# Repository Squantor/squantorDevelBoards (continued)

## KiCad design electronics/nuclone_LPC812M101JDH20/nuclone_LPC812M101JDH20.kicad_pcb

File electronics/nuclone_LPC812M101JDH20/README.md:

# Nuclone development board for LPC812M101JD20
LPC812 development board inspired by the nucleo series from STM32.
## TODO's
Still some things need to be done:
* update Readme.md with pictures and BOM (WIP)

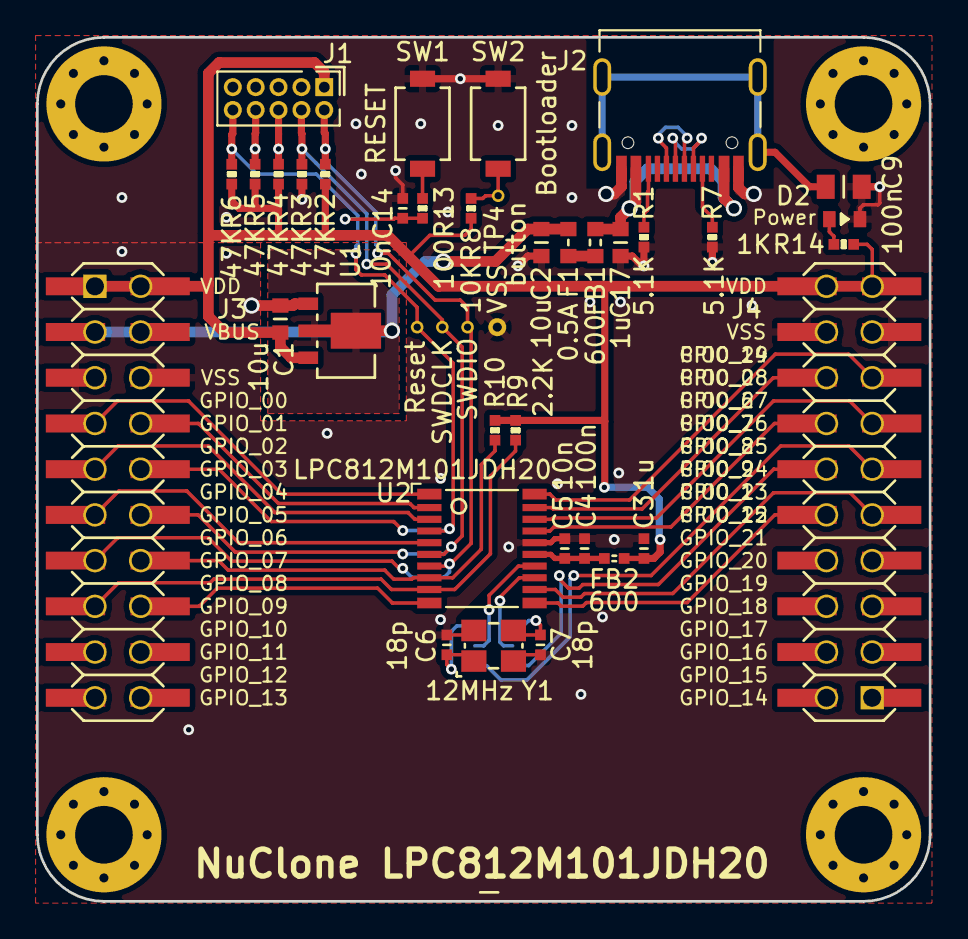
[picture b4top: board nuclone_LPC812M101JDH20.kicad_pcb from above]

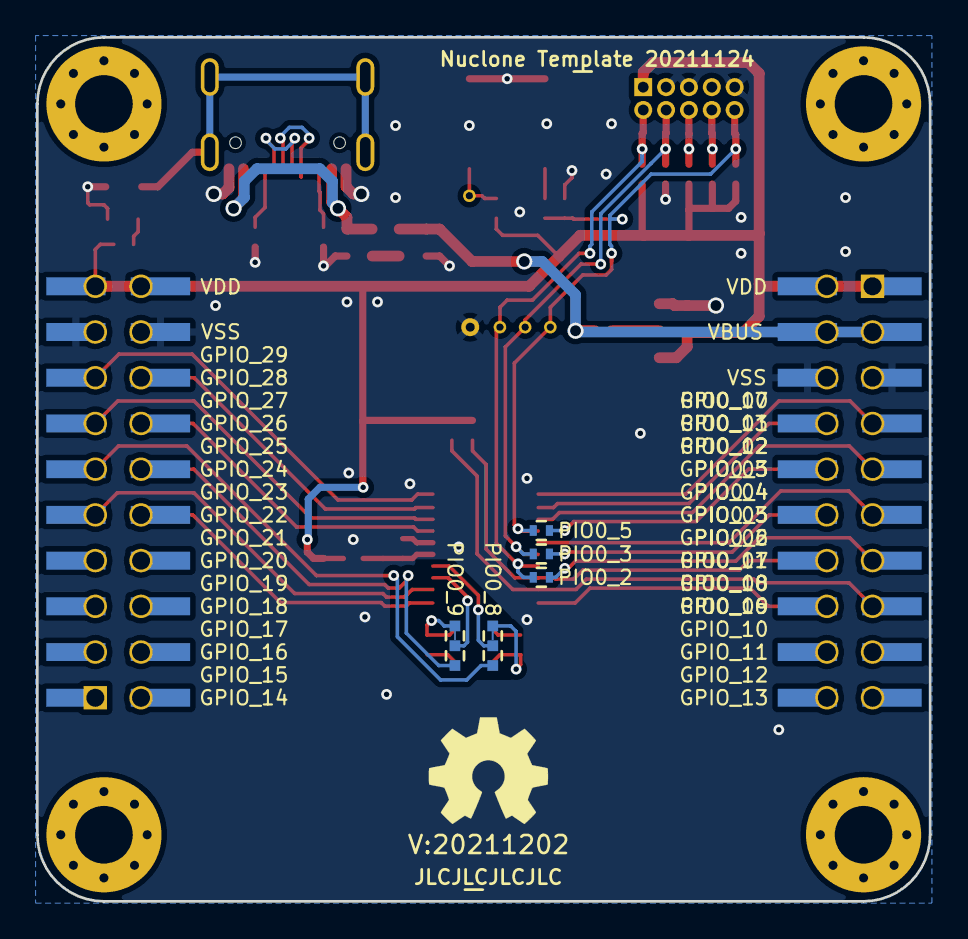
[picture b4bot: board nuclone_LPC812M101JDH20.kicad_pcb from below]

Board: 2 copper layers, 49.6 x 48.0 mm, 54 parts (9 on the bottom side), 41 nets.

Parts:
C1, C2: 10u; C_0603
C3: 1u; C_0402
C4: 100n; C_0402
C5, C14: 10n; C_0402
C6, C7: 18p; C_0402
C9: 100n; C_0805
C17: 1u; C_0603
D2: GREEN; LED_0603_hand
F1: 0.5A; F_0603_hand
FB1: 600; L_0603
FB2: 600; L_0402
H1, H2, H3, H4: MountingHole; MountingHole_3.2mm_M3_Pad_Via
J1: JTAG_2X05; Header-0127-2X05-H006
J2: TYPE-C-31-M-12; USB-C-HRO-31-M-12
J3: nuclone_small_left; nuclone_small_left_stacked
J4: nuclone_small_right; nuclone_small_right_stacked
JP1: PIO0_5; solder_jumper_2way_noconn
JP2: PIO0_3; solder_jumper_2way_noconn
JP3: PIO0_2; solder_jumper_2way_noconn
JP4: PIO0_8; solder_jumper_3way_12conn
JP5: PIO0_9; solder_jumper_3way_12conn
N1: OHWLOGO; OSHW-Symbol_6.7x6mm_SilkScreen
N2: 20211202; Label_version
N3: JLCJLCJLCJLC; Label_Generic
N4: NuClone LPC812M101JDH20; Label_Generic
N5: Nuclone Template 20211124; Label_Generic
R1, R7: 5.1K; R_0402_hand
R2, R3, R4, R5, R6: 47K; R_0402_hand
R8: 10K; R_0402_hand
R9, R10: 2.2K; R_0402_hand
R13: 100; R_0402_hand
R14: 1K; R_0402_hand
SW1: RESET; TD-85XU
SW2: Bootloader; TD-85XU
TP1: SWDIO; TestPoint_hole_H04R07
TP2: SWDCLK; TestPoint_hole_H04R07
TP3: VSS; TestPoint_hole_H05R10
TP4: button; TestPoint_hole_H04R07
TP5: Reset; TestPoint_hole_H04R07
U1: MCP1702-MB; SOT89-NXP
U2: LPC812M101JDH20; SOT360-NXP
Y1: 12MHz; Crystal_3225_4

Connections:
/Bootloader: R8.1, SW2.2, TP4.1
/GPIO_00: J3.7 (GPIO_00), U2.1 (PIO0_17)
/GPIO_01: J3.8 (GPIO_01), U2.2 (PIO0_13)
/GPIO_02: J3.9 (GPIO_02), U2.3 (PIO0_12)
/GPIO_03: J3.10 (GPIO_03), JP1.1
/GPIO_04: J3.11 (GPIO_04), U2.5 (PIO0_4/WAKEUP/#TRST)
/GPIO_05: J3.12 (GPIO_05), JP2.1
/GPIO_06: J3.13 (GPIO_06), JP3.1
/GPIO_07: J3.14 (GPIO_07), R10.1, U2.8 (PIO0_11/I2C)
/GPIO_08: J3.15 (GPIO_08), R9.1, U2.9 (PIO0_10/I2C)
/GPIO_09: J3.16 (GPIO_09), U2.10 (PIO0_16)
/GPIO_22: J4.10 (GPIO_22), U2.11 (PIO0_15)
/GPIO_23: J4.9 (GPIO_23), U2.12 (PIO0_1/ACMP_I2/CLKIN/TDI)
/GPIO_24: J4.12 (GPIO_24), JP5.3
/GPIO_25: J4.11 (GPIO_25), JP4.3
/GPIO_26: J4.14 (GPIO_26), U2.17 (PIO0_7)
/GPIO_27: J4.13 (GPIO_27), U2.18 (PIO0_6/VDDCMP)
/GPIO_28: J4.16 (GPIO_28), U2.19 (PIO0_0/ACMP_I1/TDO)
/GPIO_29: J4.15 (GPIO_29), U2.20 (PIO0_14)
/RESET: C14.2, J1.10 (nRESET), JP1.2, R6.1, R13.1, TP5.1, U2.4 (#RESET/PIO0_5)
/TCK: J1.4 (SWDCLK/TCK), JP2.2, R3.1, TP2.1, U2.6 (SWCLK/PIO0_3/TCK)
/TDI: J1.8 (TDI), R5.1
/TDO: J1.6 (SWO/TDO), R4.1
/TMS: J1.2 (SWDIO/TMS), JP3.2, R2.1, TP1.1, U2.7 (SWDIO/PIO0_2/TMS)
/VBUS: C2.2, F1.1, J3.3 (VBUS), J3.4 (VBUS), U1.2 (Vin)
/VDD: C1.1, C3.1, FB2.2, J1.1 (VCC), J3.1 (VDD), J3.2 (VDD), J4.19 (VDD), J4.20 (VDD), R2.2, R4.2, R5.2, R6.2, R8.2, R9.2, R10.2, R14.2, U1.3 (Vout)
/VSS: C1.2, C2.1, C3.2, C4.2, C5.2, C6.2, C7.2, C9.1, C14.1, C17.1, D2.1 (K), J1.3 (GND), J1.5 (GND), J1.9 (GNDDET), J2.A1B12 (GND), J2.B1A12 (GND), J3.5 (VSS), J3.6 (VSS), J4.17 (VSS), J4.18 (VSS), R1.1, R3.2, R7.1, SW1.1, SW2.1, TP3.1, U1.1 (GND), U2.16 (VSS), Y1.2, Y1.4
/microcontroller/XTALIN: JP4.2, U2.14 (PIO0_8/XTALIN)
/microcontroller/XTALOUT: JP5.2, U2.13 (PIO0_9/XTALOUT)
unnamed: C4.1, C5.1, FB2.1, U2.15 (VDD)
unnamed: C6.1, JP4.1, Y1.1
unnamed: C7.1, JP5.1, Y1.3
unnamed: C9.2, J2.S (Shield)
unnamed: C17.2, FB1.2, J2.A4B9 (VBUS), J2.B4A9 (VBUS)
unnamed: D2.2 (A), R14.1
unnamed: F1.2, FB1.1
unnamed: J2.A5 (CC1), R7.2
unnamed: J2.A6 (DP1), J2.B6 (DP2)
unnamed: J2.A7 (DN1), J2.B7 (DN2)
unnamed: J2.B5 (CC2), R1.2
unnamed: R13.2, SW1.2

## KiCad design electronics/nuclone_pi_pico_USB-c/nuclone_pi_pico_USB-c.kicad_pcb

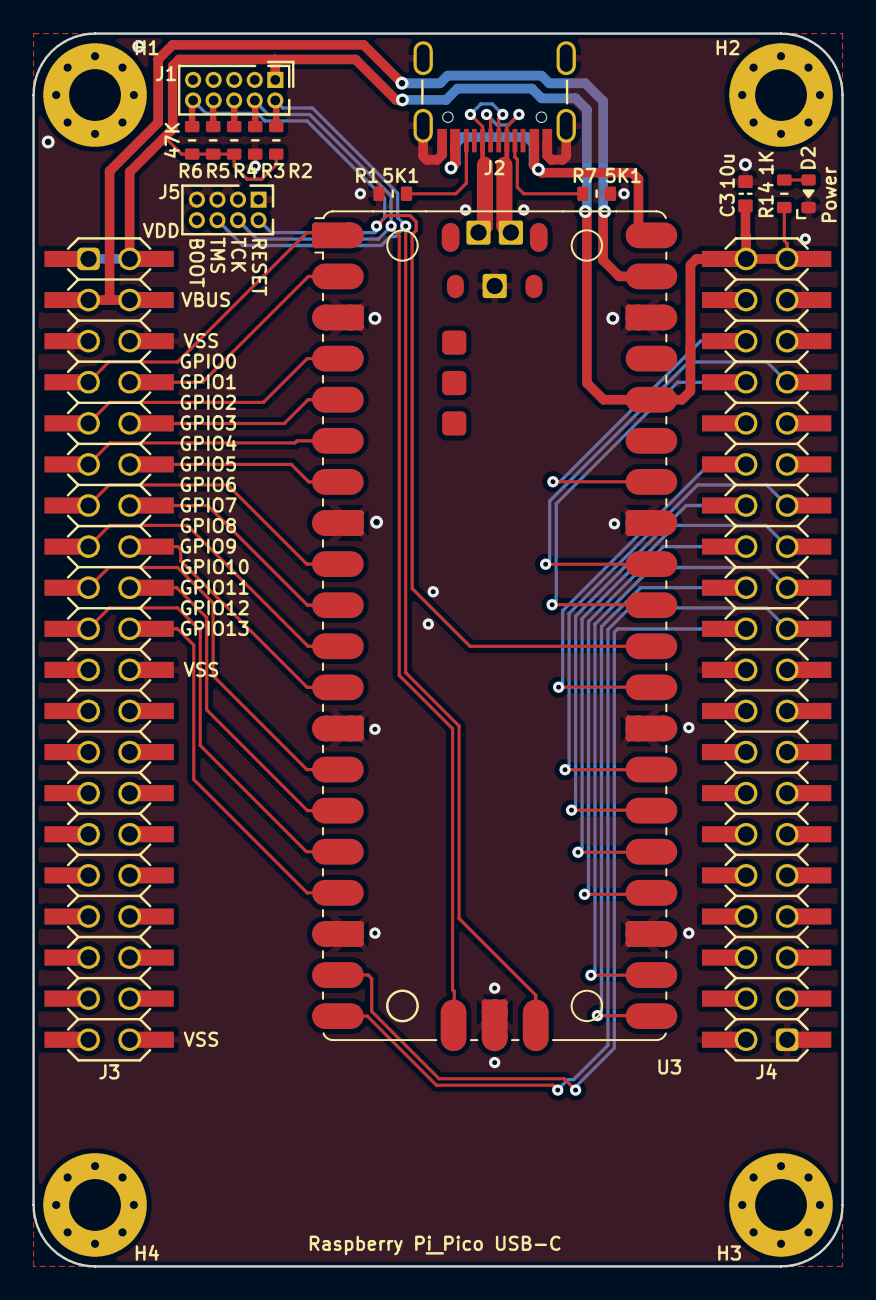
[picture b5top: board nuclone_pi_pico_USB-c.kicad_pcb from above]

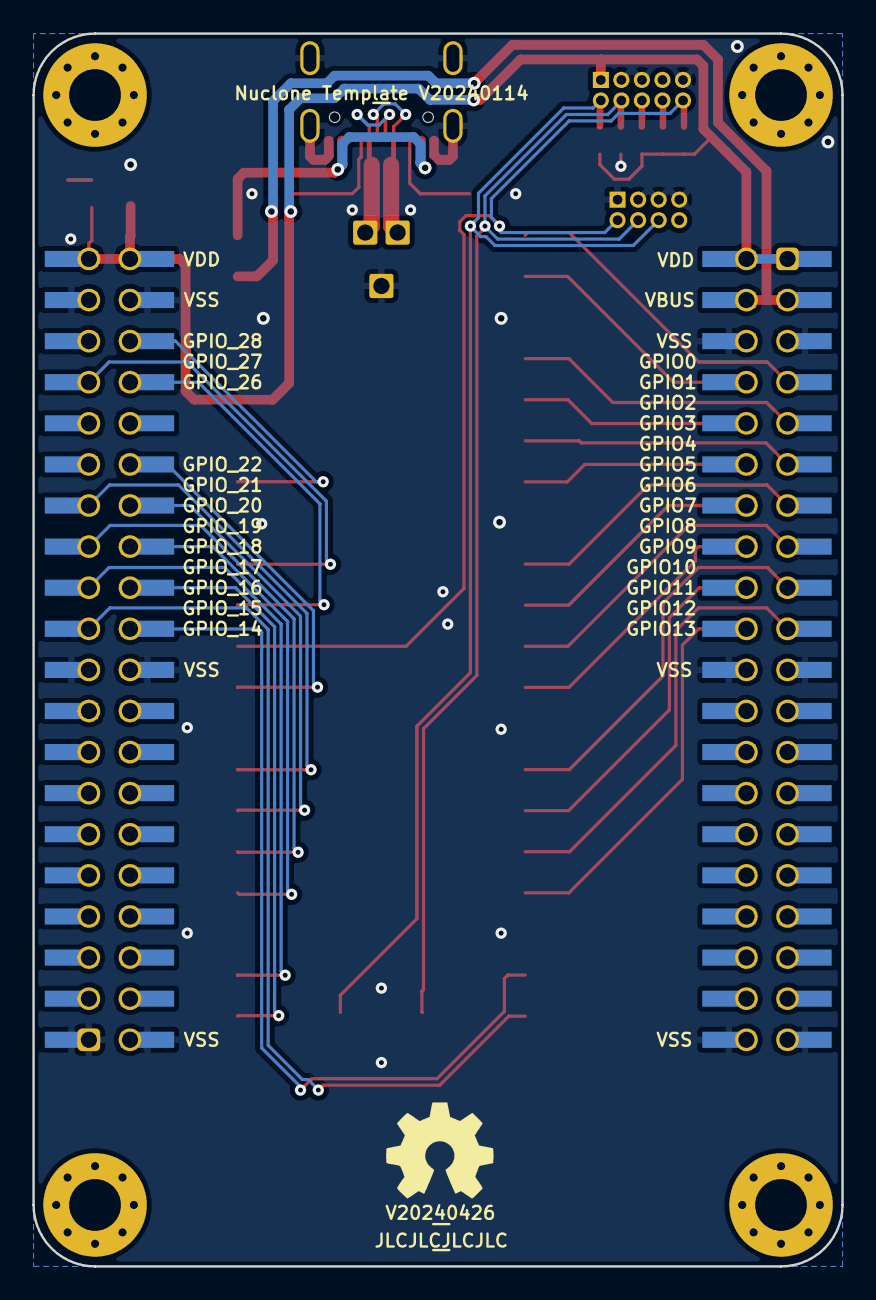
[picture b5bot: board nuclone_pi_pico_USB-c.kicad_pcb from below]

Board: 2 copper layers, 50.0 x 76.2 mm, 25 parts (4 on the bottom side), 40 nets.

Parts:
C3: 10u; C_0603
D2: GREEN; LED_0603_hand
H1, H2, H3, H4: MountingHole; MountingHole_3.2mm_M3_Pad_Via
J1: JTAG_2X05; Header-0127-2X05-H006
J2: USB-C_PD_USB; USB-C-HRO-31-M-12_aisler
J3: nuclone_medium_left; nuclone_medium_left_stacked
J4: nuclone_medium_right; nuclone_medium_right_stacked
J5: Conn_02x06_Odd_Even; Header-0127-2X04-H006
N1: OHWLOGO; OSHW-Symbol_6.7x6mm_SilkScreen
N2: V20240426; Label_Generic
N3: JLCJLCJLCJLC; Label_Generic
N4: Raspberry Pi Pico USB-C; Label_Generic
N5: Nuclone Template V20240114; Label_Generic
R1, R7: 5K1; R_0603_hand
R2, R3, R4, R5, R6: 47K; R_0603_hand
R14: 1K; R_0603_hand
U3: RaspberryPiPico; RaspberryPi_Pico_Original_SMD_nokeepout_USB_TP_TH

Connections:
/GPIO_00: J3.7 (GPIO_00), U3.1 (GP0)
/GPIO_01: J3.8 (GPIO_01), U3.2 (GP1)
/GPIO_02: J3.9 (GPIO_02), U3.4 (GP2)
/GPIO_03: J3.10 (GPIO_03), U3.5 (GP3)
/GPIO_04: J3.11 (GPIO_04), U3.6 (GP4)
/GPIO_05: J3.12 (GPIO_05), U3.7 (GP5)
/GPIO_06: J3.13 (GPIO_06), U3.9 (GP6)
/GPIO_07: J3.14 (GPIO_07), U3.10 (GP7)
/GPIO_08: J3.15 (GPIO_08), U3.11 (GP8)
/GPIO_09: J3.16 (GPIO_09), U3.12 (GP9)
/GPIO_10: J3.17 (GPIO_10), U3.14 (GP10)
/GPIO_11: J3.18 (GPIO_11), U3.15 (GP11)
/GPIO_12: J3.19 (GPIO_12), U3.16 (GP12)
/GPIO_13: J3.20 (GPIO_13), U3.17 (GP13)
/GPIO_46: J4.22 (GPIO_46), U3.19 (GP14)
/GPIO_47: J4.21 (GPIO_47), U3.20 (GP15)
/GPIO_48: J4.24 (GPIO_48), U3.21 (GP16)
/GPIO_49: J4.23 (GPIO_49), U3.22 (GP17)
/GPIO_50: J4.26 (GPIO_50), U3.24 (GP18)
/GPIO_51: J4.25 (GPIO_51), U3.25 (GP19)
/GPIO_52: J4.28 (GPIO_52), U3.26 (GP20)
/GPIO_53: J4.27 (GPIO_53), U3.27 (GP21)
/GPIO_54: J4.30 (GPIO_54), U3.29 (GP22)
/GPIO_58: J4.34 (GPIO_58), U3.31 (GP26_A0)
/GPIO_59: J4.33 (GPIO_59), U3.32 (GP27_A1)
/GPIO_60: J4.36 (GPIO_60), U3.34 (GP28_A2)
/RESET: J1.10 (nRESET), J5.2, R6.1, U3.30 (RUN)
/TCK: J1.4 (SWDCLK/TCK), J5.4, R3.1, U3.D1 (SWCLK)
/TDI: J1.8 (TDI), R5.1
/TDO: J1.6 (SWO/TDO), R4.1
/TMS: J1.2 (SWDIO/TMS), J5.6, R2.1, U3.D3 (SWDIO)
/USB_D+: J2.A6 (DP1), J2.B6 (DP2), U3.TP3 (USB_DP)
/USB_D-: J2.A7 (DN1), J2.B7 (DN2), U3.TP2 (USB_DM)
/VBUS: J2.A4B9 (VBUS), J2.B4A9 (VBUS), U3.40 (VBUS)
/VDD: C3.1, J1.1 (VCC), J3.1 (VDD), J3.2 (VDD), J4.39 (VDD), J4.40 (VDD), R2.2, R4.2, R5.2, R6.2, R14.2, U3.36 (3V3)
/VSS: C3.2, D2.1 (K), J1.3 (GND), J1.5 (GND), J1.9 (GNDDET), J2.A1B12 (GND), J2.B1A12 (GND), J2.S (Shield), J3.5 (VSS), J3.6 (VSS), J3.21 (VSS), J3.22 (VSS), J3.39 (VSS), J3.40 (VSS), J4.1 (VSS), J4.2 (VSS), J4.19 (VSS), J4.20 (VSS), J4.37 (VSS), J4.38 (VSS), J5.1, J5.3, J5.5, J5.7, R1.1, R3.2, R7.1, U3.3 (GND), U3.8 (GND), U3.13 (GND), U3.18 (GND), U3.23 (GND), U3.28 (GND), U3.33 (AGND), U3.38 (GND), U3.D2 (GND), U3.TP1 (GND)
/VSYS: J3.3 (VBUS), J3.4 (VBUS), U3.39 (VSYS)
unnamed: D2.2 (A), R14.1
unnamed: J2.A5 (CC1), R7.2
unnamed: J2.B5 (CC2), R1.2

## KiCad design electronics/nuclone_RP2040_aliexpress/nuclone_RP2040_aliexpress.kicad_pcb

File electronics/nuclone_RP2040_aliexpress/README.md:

# nuclone raspberry pi pico
Medium sized nuclone fitted with a raspberry pi pico soldered on board, the pico micro USB is used as the board connection.
# HSI (Hardware Software Interface)
## TODO's
Still some things need to be done:
* schematic entry 
* PCB layout
* Review with one night in between
* Produce at [OSHPARK](https://oshpark.com/)
* Assemble
* Test & characterise
* update Readme.md with pictures and BOM
## BOM
* Raspberry pi pico
## Pictures

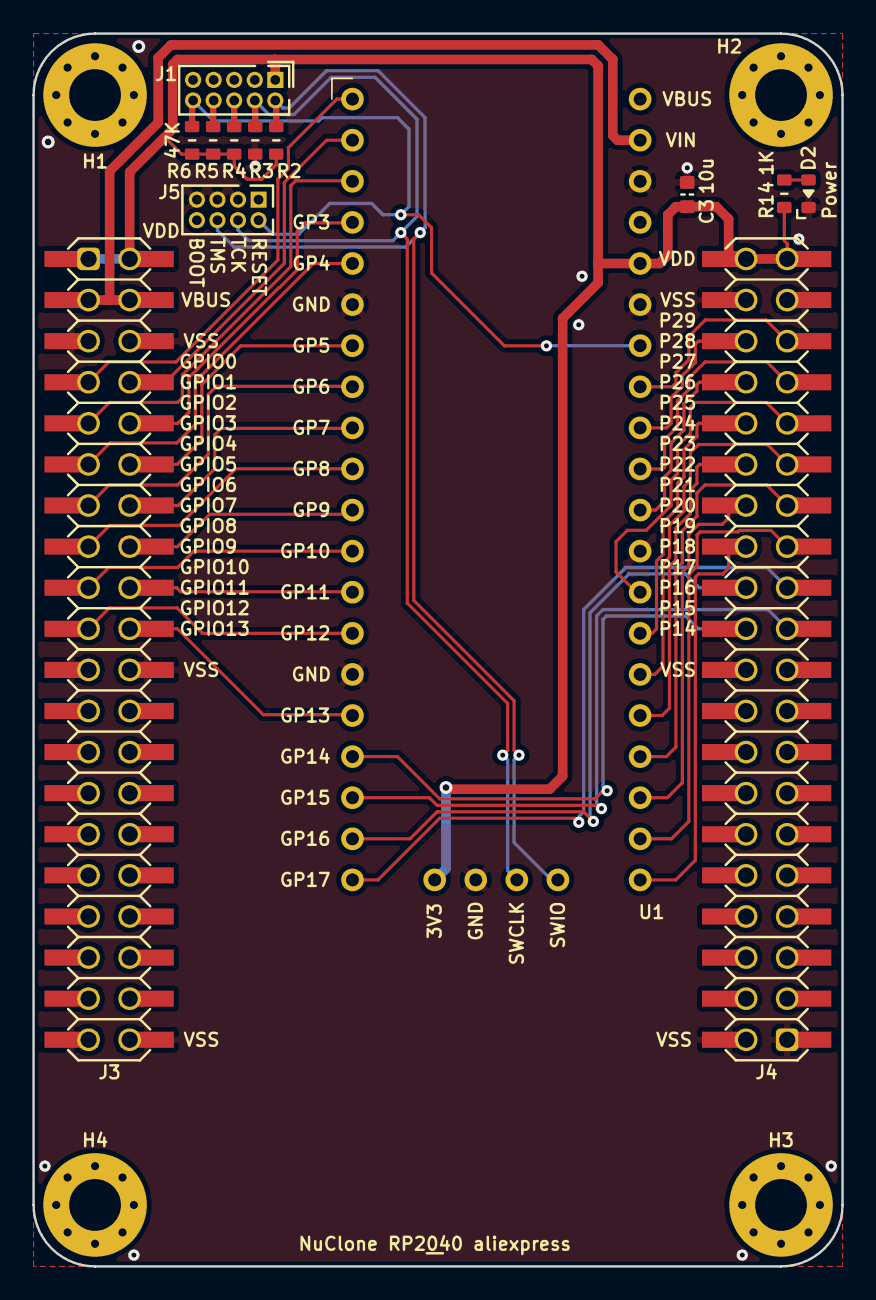
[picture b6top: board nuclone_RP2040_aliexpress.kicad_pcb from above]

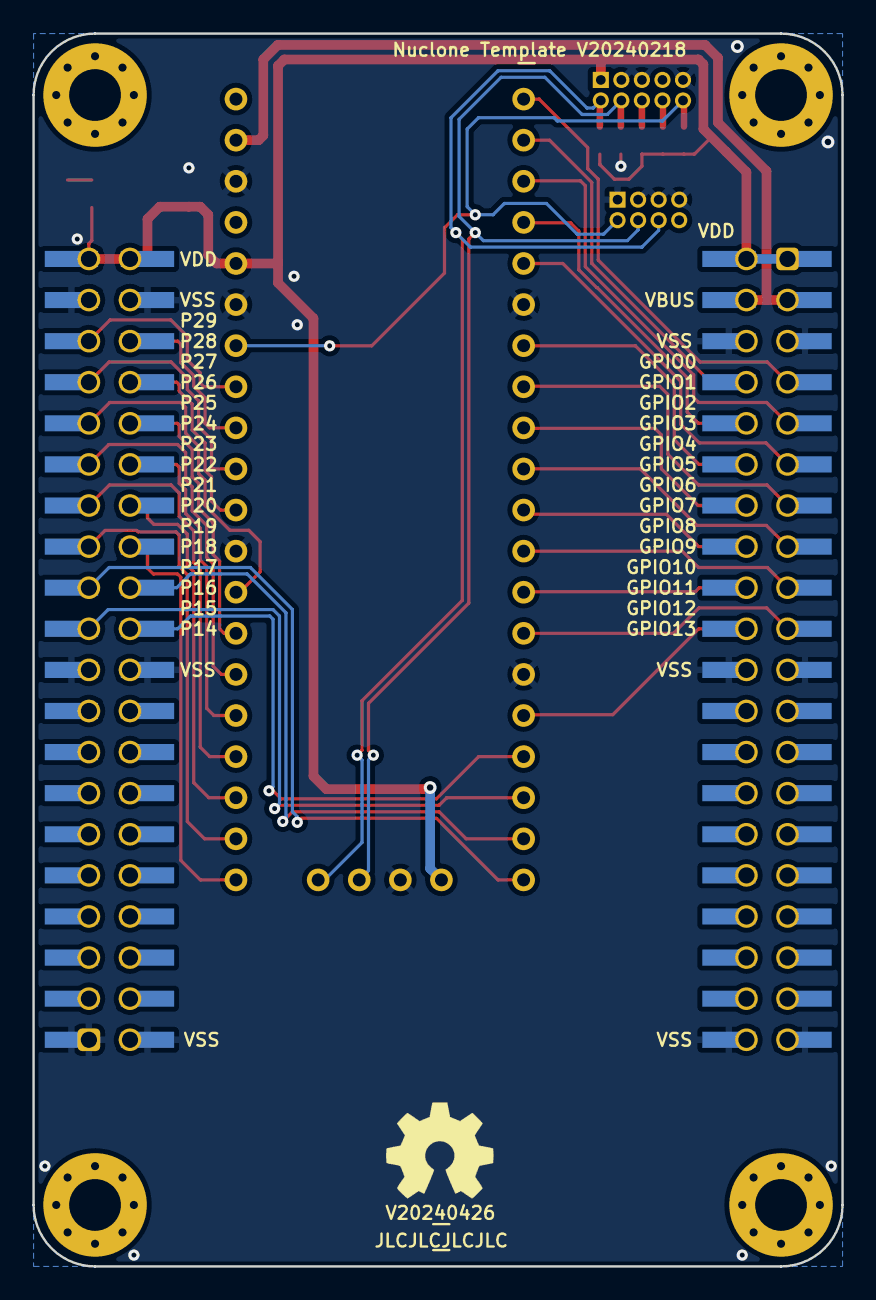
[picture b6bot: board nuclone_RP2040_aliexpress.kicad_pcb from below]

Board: 2 copper layers, 50.0 x 76.2 mm, 22 parts (4 on the bottom side), 39 nets.

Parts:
C3: 10u; C_0603
D2: GREEN; LED_0603_hand
H1, H2, H3, H4: MountingHole; MountingHole_3.2mm_M3_Pad_Via
J1: JTAG_2X05; Header-0127-2X05-H006
J3: nuclone_medium_left; nuclone_medium_left_stacked
J4: nuclone_medium_right; nuclone_medium_right_stacked
J5: Conn_02x06_Odd_Even; Header-0127-2X04-H006
N1: OHWLOGO; OSHW-Symbol_6.7x6mm_SilkScreen
N2: V20240426; Label_Generic
N3: JLCJLCJLCJLC; Label_Generic
N4: NuClone RP2040 aliexpress; Label_Generic
N5: Nuclone Template V20240218; Label_Generic
R2, R3, R4, R5, R6: 47K; R_0603_hand
R14: 1K; R_0603_hand
U1: RP2040_aliexpress; module_rp2040_aliexpress

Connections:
/GPIO_00: J3.7 (GPIO_00), U1.1 (GP0)
/GPIO_01: J3.8 (GPIO_01), U1.2 (GP1)
/GPIO_02: J3.9 (GPIO_02), U1.3 (GP2)
/GPIO_03: J3.10 (GPIO_03), U1.4 (GP3)
/GPIO_04: J3.11 (GPIO_04), U1.5 (GP4)
/GPIO_05: J3.12 (GPIO_05), U1.7 (GP5)
/GPIO_06: J3.13 (GPIO_06), U1.8 (GP6)
/GPIO_07: J3.14 (GPIO_07), U1.9 (GP7)
/GPIO_08: J3.15 (GPIO_08), U1.10 (GP8)
/GPIO_09: J3.16 (GPIO_09), U1.11 (GP9)
/GPIO_10: J3.17 (GPIO_10), U1.12 (GP10)
/GPIO_11: J3.18 (GPIO_11), U1.13 (GP11)
/GPIO_12: J3.19 (GPIO_12), U1.14 (GP12)
/GPIO_13: J3.20 (GPIO_13), U1.16 (GP13)
/GPIO_46: J4.22 (GPIO_46), U1.17 (GP14)
/GPIO_47: J4.21 (GPIO_47), U1.18 (GP15)
/GPIO_48: J4.24 (GPIO_48), U1.19 (GP16)
/GPIO_49: J4.23 (GPIO_49), U1.20 (GP17)
/GPIO_50: J4.26 (GPIO_50), U1.21 (GP18)
/GPIO_51: J4.25 (GPIO_51), U1.22 (GP19)
/GPIO_52: J4.28 (GPIO_52), U1.23 (GP20)
/GPIO_53: J4.27 (GPIO_53), U1.24 (GP21)
/GPIO_54: J4.30 (GPIO_54), U1.25 (GP22)
/GPIO_55: J4.29 (GPIO_55), U1.26 (GP23)
/GPIO_56: J4.32 (GPIO_56), U1.27 (GP24)
/GPIO_57: J4.31 (GPIO_57), U1.28 (GP25)
/GPIO_58: J4.34 (GPIO_58), U1.30 (GP26_A0)
/GPIO_59: J4.33 (GPIO_59), U1.31 (GP27_A1)
/GPIO_60: J4.36 (GPIO_60), U1.32 (GP28_A2)
/GPIO_61: J4.35 (GPIO_61), U1.33 (GP29_A3)
/RESET: J1.10 (nRESET), J5.2, R6.1, U1.34 (RUN)
/TCK: J1.4 (SWDCLK/TCK), J5.4, R3.1, U1.43 (SWCLK)
/TDI: J1.8 (TDI), R5.1
/TDO: J1.6 (SWO/TDO), R4.1
/TMS: J1.2 (SWDIO/TMS), J5.6, R2.1, U1.44 (SWDIO)
/VBUS: J3.3 (VBUS), J3.4 (VBUS), U1.39 (VIN)
/VDD: C3.1, J1.1 (VCC), J3.1 (VDD), J3.2 (VDD), J4.39 (VDD), J4.40 (VDD), R2.2, R4.2, R5.2, R6.2, R14.2, U1.36 (3V3), U1.41 (3V3)
/VSS: C3.2, D2.1 (K), J1.3 (GND), J1.5 (GND), J1.9 (GNDDET), J3.5 (VSS), J3.6 (VSS), J3.21 (VSS), J3.22 (VSS), J3.39 (VSS), J3.40 (VSS), J4.1 (VSS), J4.2 (VSS), J4.19 (VSS), J4.20 (VSS), J4.37 (VSS), J4.38 (VSS), J5.1, J5.3, J5.5, J5.7, R3.2, U1.6 (GND), U1.15 (GND), U1.29 (AGND), U1.35 (GND), U1.38 (GND), U1.42 (GND)
unnamed: D2.2 (A), R14.1

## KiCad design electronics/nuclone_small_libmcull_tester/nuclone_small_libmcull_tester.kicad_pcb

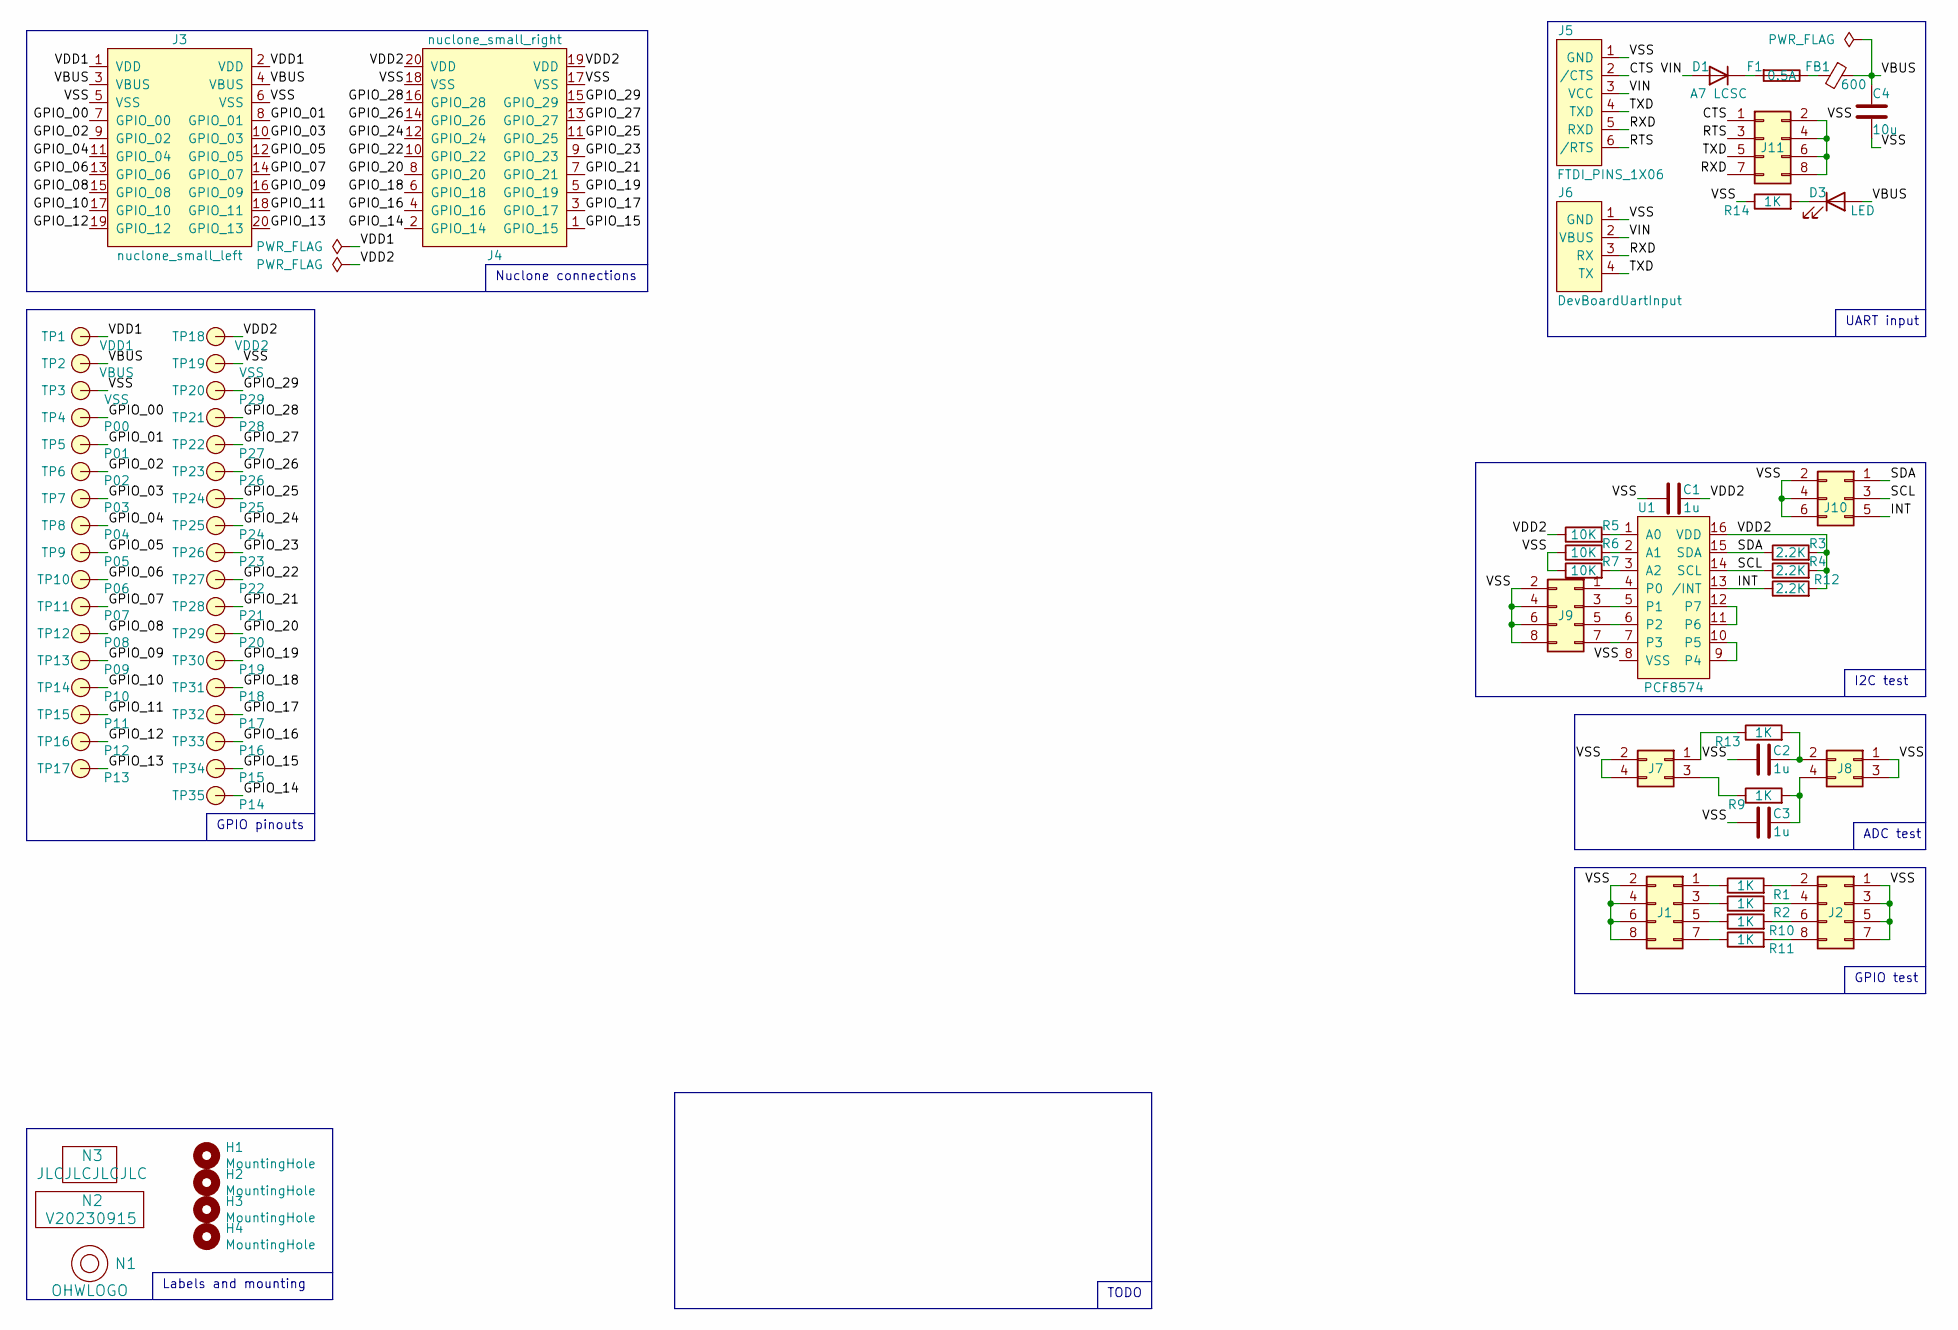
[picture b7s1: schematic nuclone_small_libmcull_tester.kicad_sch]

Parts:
C1: 1u; C_0603
C2, C3: 1u; C_0805+0603
C4: 10u; C_0603
D1: A7 LCSC; SOD-123F-hand
D3: LED; LED_0603_hand
F1: 0.5A; F_0603_hand
FB1: 600; L_0603
H1, H2, H3, H4: MountingHole; MountingHole_3.2mm_M3_Pad_Via
J1, J2, J9, J11: Conn_02x04_Odd_Even; Header-0254-2X04-H010
J3: nuclone_small_left; nuclone_small_left_stacked
J4: nuclone_small_right; nuclone_small_right_stacked
J5: FTDI_PINS_1X06; Header-0254-1X06-H010
J6: DevBoardUartInput; JST_PH_B4B-PH-K_1x04_P2.00mm_Vertical
J7, J8: Conn_02x02_Odd_Even; Header-0254-2X02-H010
J10: Conn_02x03_Odd_Even; Header-0254-2X03-H010
N1: OHWLOGO; OSHW-Symbol_6.7x6mm_SilkScreen
N2: V20230915; Label_Generic
N3: JLCJLCJLCJLC; Label_Generic
R1, R2, R9, R10, R11, R13: 1K; R_0805+0603
R3, R4, R12: 2.2K; R_0603_hand
R5, R6, R7: 10K; R_0603_hand
R14: 1K; R_0603_hand
TP1: VDD1; TestPoint_hole_H05R10_2side
TP2: VBUS; TestPoint_hole_H05R10_2side
TP3, TP19: VSS; TestPoint_hole_H05R10_2side
TP4: P00; TestPoint_hole_H05R10_2side
TP5: P01; TestPoint_hole_H05R10_2side
TP6: P02; TestPoint_hole_H05R10_2side
TP7: P03; TestPoint_hole_H05R10_2side
TP8: P04; TestPoint_hole_H05R10_2side
TP9: P05; TestPoint_hole_H05R10_2side
TP10: P06; TestPoint_hole_H05R10_2side
TP11: P07; TestPoint_hole_H05R10_2side
TP12: P08; TestPoint_hole_H05R10_2side
TP13: P09; TestPoint_hole_H05R10_2side
TP14: P10; TestPoint_hole_H05R10_2side
TP15: P11; TestPoint_hole_H05R10_2side
TP16: P12; TestPoint_hole_H05R10_2side
TP17: P13; TestPoint_hole_H05R10_2side
TP18: VDD2; TestPoint_hole_H05R10_2side
TP20: P29; TestPoint_hole_H05R10_2side
TP21: P28; TestPoint_hole_H05R10_2side
TP22: P27; TestPoint_hole_H05R10_2side
TP23: P26; TestPoint_hole_H05R10_2side
TP24: P25; TestPoint_hole_H05R10_2side
TP25: P24; TestPoint_hole_H05R10_2side
TP26: P23; TestPoint_hole_H05R10_2side
TP27: P22; TestPoint_hole_H05R10_2side
TP28: P21; TestPoint_hole_H05R10_2side
TP29: P20; TestPoint_hole_H05R10_2side
TP30: P19; TestPoint_hole_H05R10_2side
TP31: P18; TestPoint_hole_H05R10_2side
TP32: P17; TestPoint_hole_H05R10_2side
TP33: P16; TestPoint_hole_H05R10_2side
TP34: P15; TestPoint_hole_H05R10_2side
TP35: P14; TestPoint_hole_H05R10_2side
U1: PCF8574; SOIC-16W_7.5x10.3mm_P1.27mm

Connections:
/CTS: J5.2 (/CTS), J11.1
/GPIO_00: J3.7 (GPIO_00), TP4.1
/GPIO_01: J3.8 (GPIO_01), TP5.1
/GPIO_02: J3.9 (GPIO_02), TP6.1
/GPIO_03: J3.10 (GPIO_03), TP7.1
/GPIO_04: J3.11 (GPIO_04), TP8.1
/GPIO_05: J3.12 (GPIO_05), TP9.1
/GPIO_06: J3.13 (GPIO_06), TP10.1
/GPIO_07: J3.14 (GPIO_07), TP11.1
/GPIO_08: J3.15 (GPIO_08), TP12.1
/GPIO_09: J3.16 (GPIO_09), TP13.1
/GPIO_10: J3.17 (GPIO_10), TP14.1
/GPIO_11: J3.18 (GPIO_11), TP15.1
/GPIO_12: J3.19 (GPIO_12), TP16.1
/GPIO_13: J3.20 (GPIO_13), TP17.1
/GPIO_14: J4.2 (GPIO_14), TP35.1
/GPIO_15: J4.1 (GPIO_15), TP34.1
/GPIO_16: J4.4 (GPIO_16), TP33.1
/GPIO_17: J4.3 (GPIO_17), TP32.1
/GPIO_18: J4.6 (GPIO_18), TP31.1
/GPIO_19: J4.5 (GPIO_19), TP30.1
/GPIO_20: J4.8 (GPIO_20), TP29.1
/GPIO_21: J4.7 (GPIO_21), TP28.1
/GPIO_22: J4.10 (GPIO_22), TP27.1
/GPIO_23: J4.9 (GPIO_23), TP26.1
/GPIO_24: J4.12 (GPIO_24), TP25.1
/GPIO_25: J4.11 (GPIO_25), TP24.1
/GPIO_26: J4.14 (GPIO_26), TP23.1
/GPIO_27: J4.13 (GPIO_27), TP22.1
/GPIO_28: J4.16 (GPIO_28), TP21.1
/GPIO_29: J4.15 (GPIO_29), TP20.1
/INT: J10.5, R12.1, U1.13 (/INT)
/RTS: J5.6 (/RTS), J11.3
/RXD: J5.5 (RXD), J6.3 (RX), J11.7
/SCL: J10.3, R4.1, U1.14 (SCL)
/SDA: J10.1, R3.1, U1.15 (SDA)
/TXD: J5.4 (TXD), J6.4 (TX), J11.5
/VBUS: C4.1, D3.2 (A), FB1.1, J3.3 (VBUS), J3.4 (VBUS), TP2.1
/VDD1: J3.1 (VDD), J3.2 (VDD), TP1.1
/VDD2: C1.2, J4.19 (VDD), J4.20 (VDD), R3.2, R4.2, R5.1, R12.2, TP18.1, U1.16 (VDD)
/VIN: D1.2 (A), J5.3 (VCC), J6.2 (VBUS)
/VSS: C1.1, C2.1, C3.1, C4.2, J1.2, J1.4, J1.6, J1.8, J2.1, J2.3, J2.5, J2.7, J3.5 (VSS), J3.6 (VSS), J4.17 (VSS), J4.18 (VSS), J5.1 (GND), J6.1 (GND), J7.2, J7.4, J8.1, J8.3, J9.2, J9.4, J9.6, J9.8, J10.2, J10.4, J10.6, J11.2, J11.4, J11.6, J11.8, R6.1, R7.1, R14.1, TP3.1, TP19.1, U1.8 (VSS)
unnamed: D1.1 (K), F1.2
unnamed: D3.1 (K), R14.2
unnamed: F1.1, FB1.2
unnamed: J1.1, R1.1
unnamed: J1.3, R2.1
unnamed: J1.5, R10.1
unnamed: J1.7, R11.1
unnamed: J2.2, R1.2
unnamed: J2.4, R2.2
unnamed: J2.6, R10.2
unnamed: J2.8, R11.2
unnamed: J7.1, R13.1
unnamed: J7.3, R9.1
unnamed: C2.2, J8.2, R13.2
unnamed: C3.2, J8.4, R9.2
unnamed: J9.1, U1.4 (P0)
unnamed: J9.3, U1.5 (P1)
unnamed: J9.5, U1.6 (P2)
unnamed: J9.7, U1.7 (P3)
unnamed: R5.2, U1.1 (A0)
unnamed: R6.2, U1.2 (A1)
unnamed: R7.2, U1.3 (A2)
unnamed: U1.9 (P4), U1.10 (P5)
unnamed: U1.11 (P6), U1.12 (P7)

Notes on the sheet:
I2C test
GPIO test
Labels and mounting
TODO
GPIO pinouts
Nuclone connections
UART input
ADC test

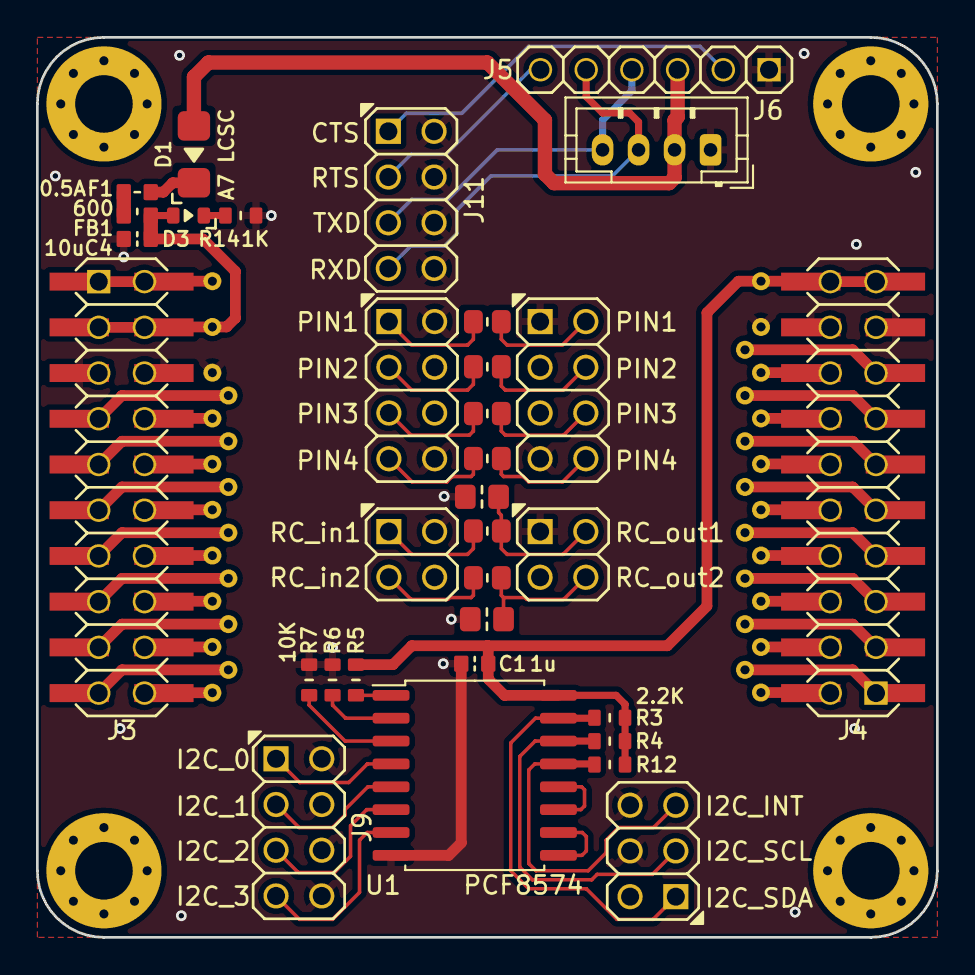
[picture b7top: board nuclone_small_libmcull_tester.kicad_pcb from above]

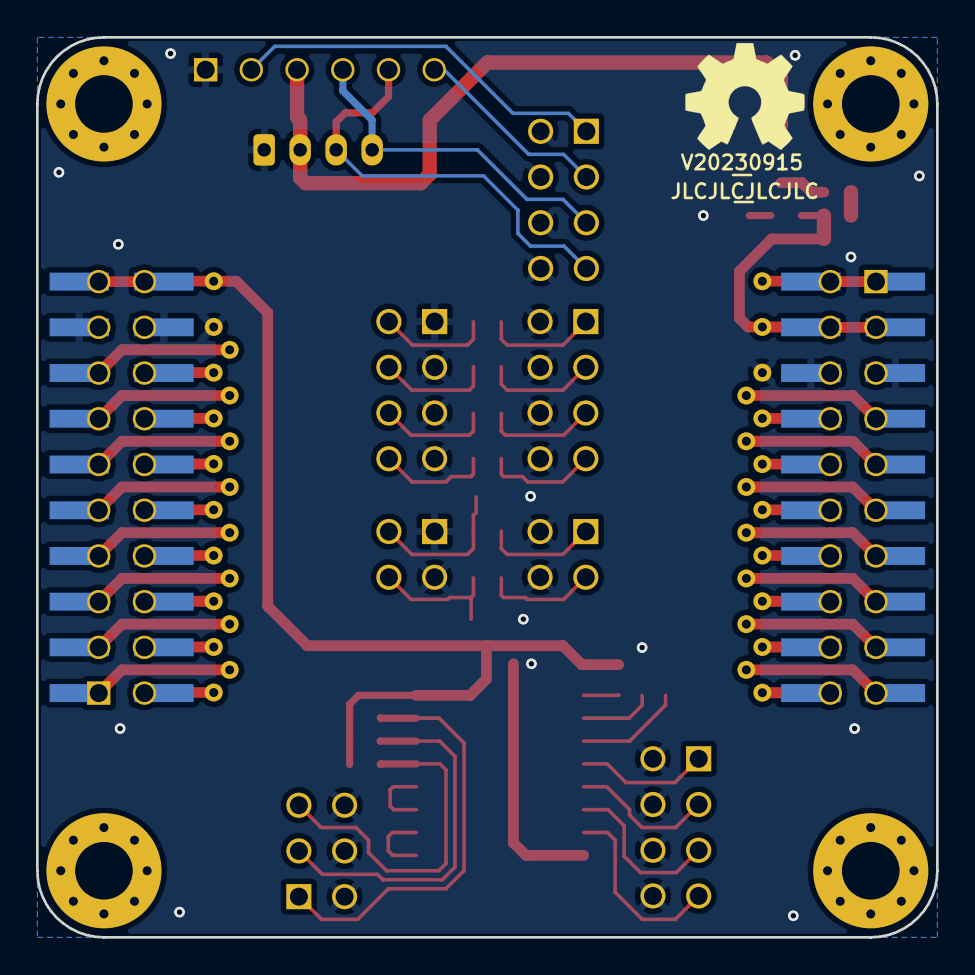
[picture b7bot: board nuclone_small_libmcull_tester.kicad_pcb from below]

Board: 2 copper layers, 50.0 x 50.0 mm, 75 parts (3 on the bottom side), 66 nets.
